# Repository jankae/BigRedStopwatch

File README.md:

# What is it?
* A huge stopwatch with two big red control buttons (start and stop)
* Mainly intended for measuring time on an obstacle course

# How does it work?
* Each button and the display contain a radio module (RFM69)
* Button presses are send to the display which calculates the time

# Further features
* USB charging of the integrated LiPo batteries
* Retransmissions with time compensation if a radio packet gets lost
* Simple highscore management

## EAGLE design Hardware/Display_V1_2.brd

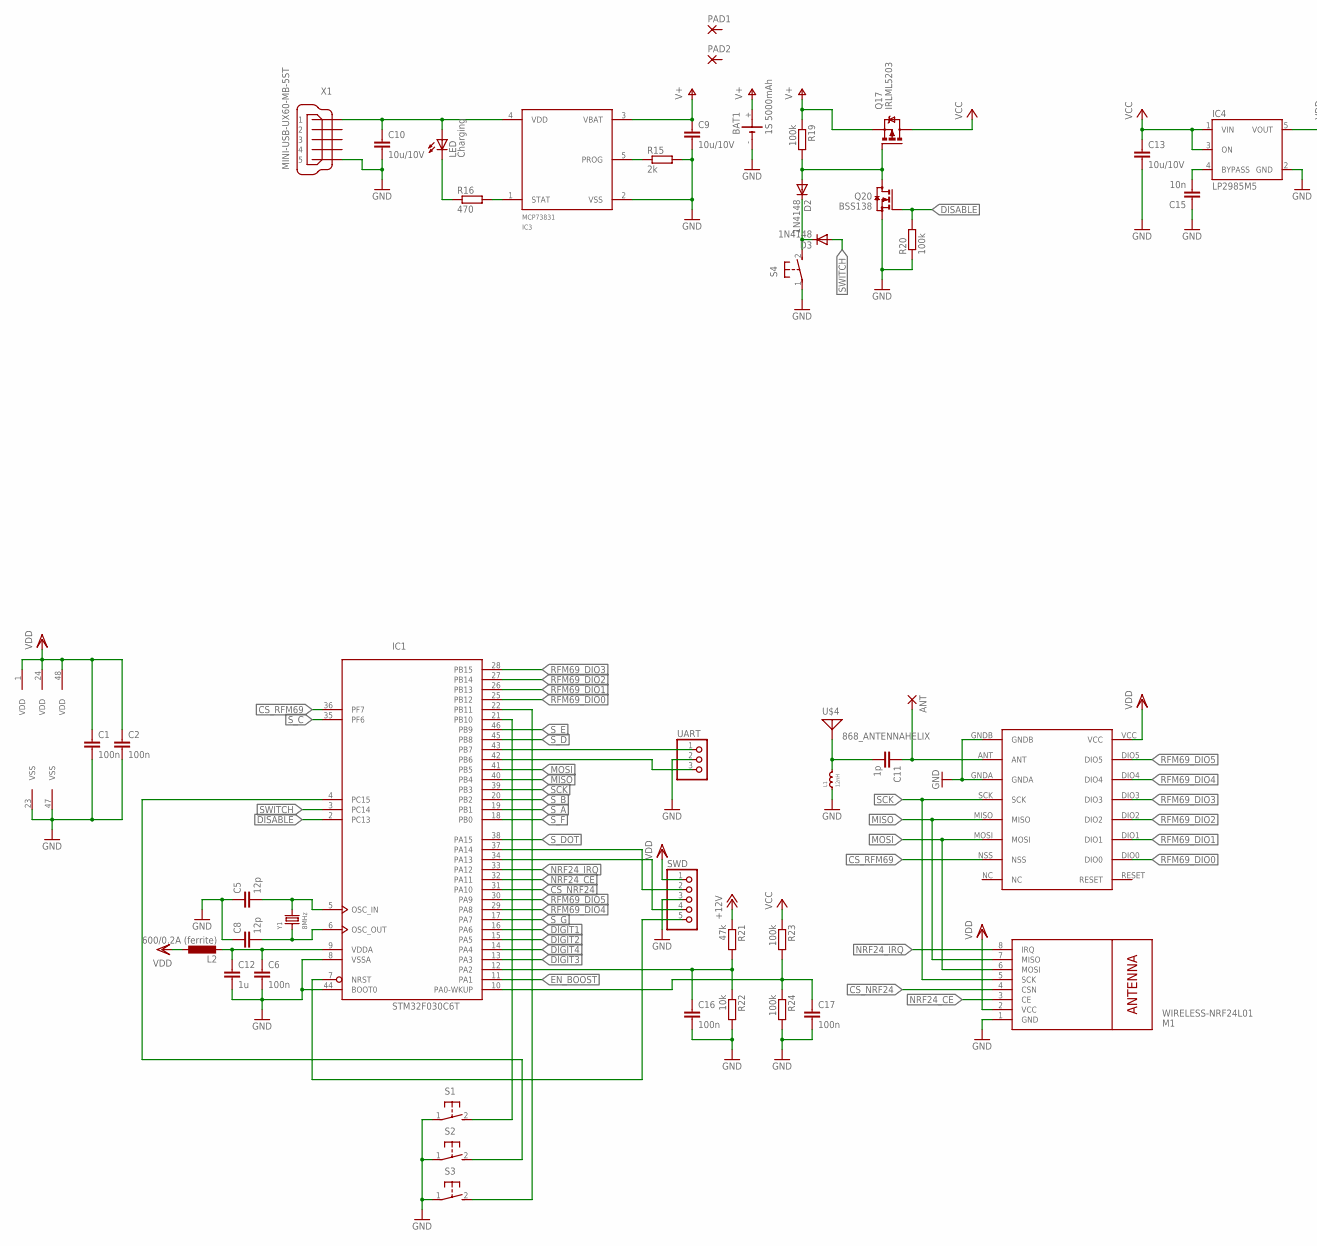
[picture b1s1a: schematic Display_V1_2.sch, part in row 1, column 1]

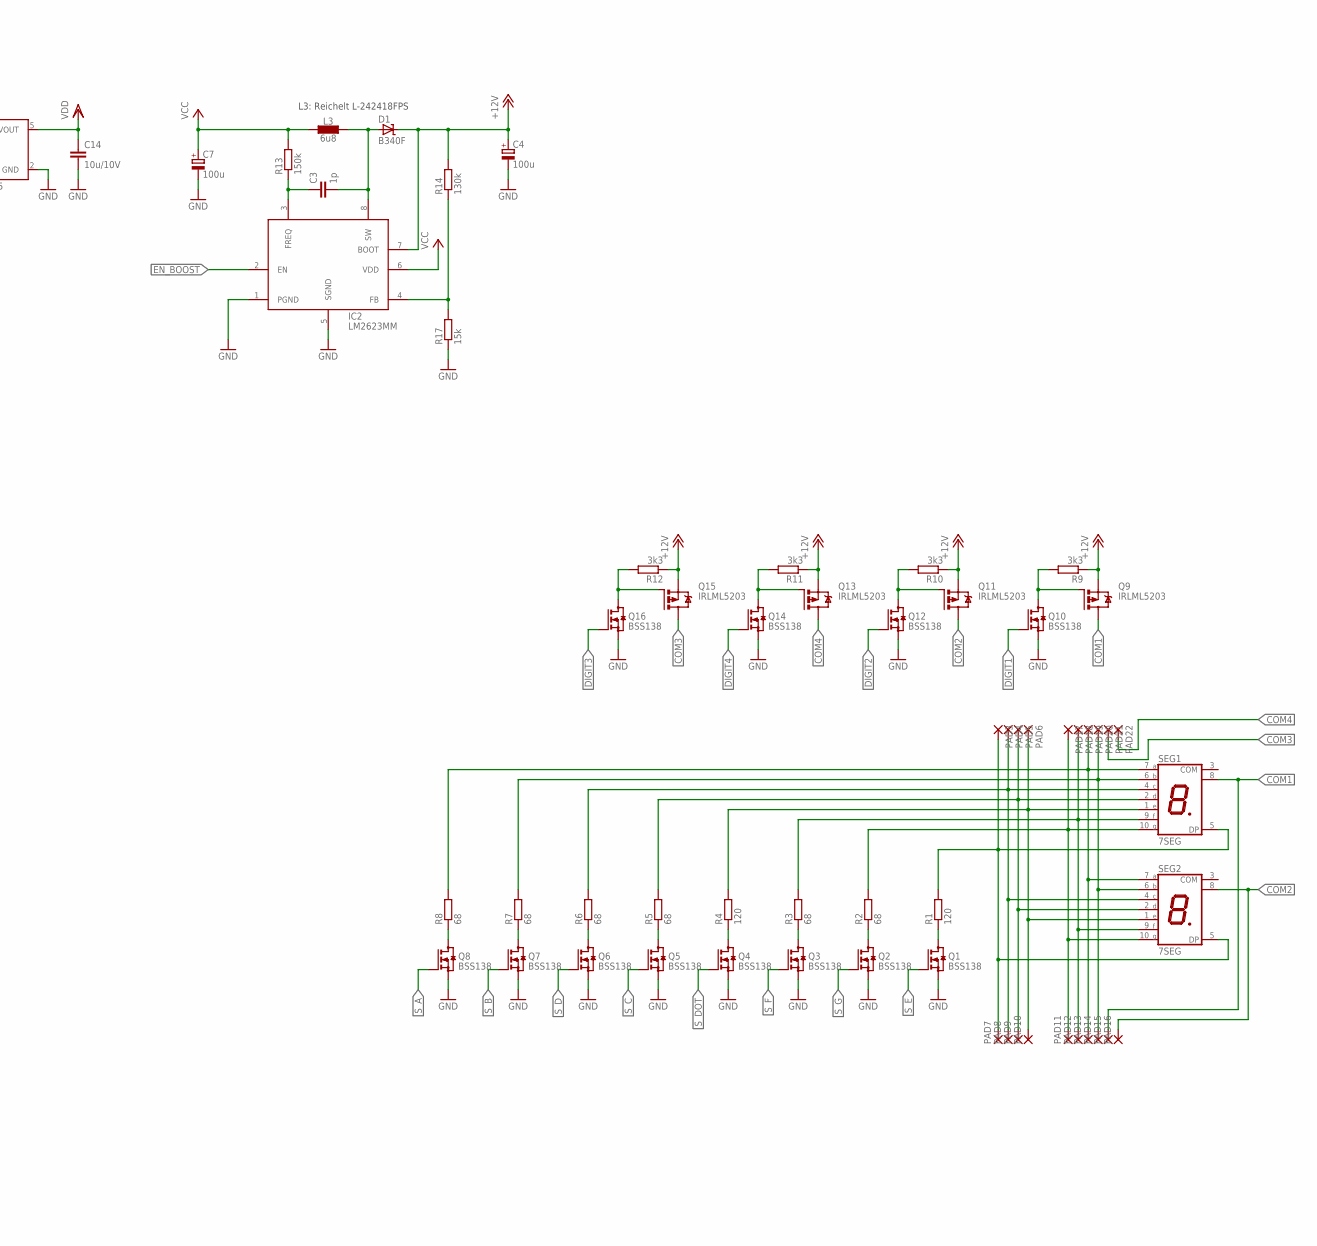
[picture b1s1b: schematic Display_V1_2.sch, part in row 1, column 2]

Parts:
ANT: 1,6/0,8
BAT1: 1S 5000mAh; 1S_5000MAH
C1, C2: 100n; C0603K
C3, C11: 1p; C0603
C4, C7: 100u; 153CLV-0605
C5, C8: 12p; C0603
C6, C16, C17: 100n; C0603
C9, C10, C13, C14: 10u/10V; C1206
C12: 1u; C0603
C15: 10n; C0603
D1: B340F; SMC
D2, D3: 1N4148; MINIMELF
IC1: STM32F030C6T; LQFP48
IC2: LM2623MM; MSOP08
IC3: MCP73831; SOT23-5
IC4: LP2985M5; SOT23-5
L1: 12nH; 0603
L2: 600/0.2A (ferrite); L2012C
L3: 6u8; L_NR60XX
LED: Charging; CHIPLED_0603
M1: WIRELESS-NRF24L01
PAD1, PAD2: 2,54/1,0
PAD3, PAD4, PAD5, PAD6, PAD7, PAD8, PAD9, PAD10, PAD11, PAD12, PAD13, PAD14, PAD15, PAD16, PAD17, PAD18, PAD19, PAD20, PAD21, PAD22: SMD2; SMD1,27-2,54
Q1, Q2, Q3, Q4, Q5, Q6, Q7, Q8, Q10, Q12, Q14, Q16, Q20: BSS138; SOT23
Q9, Q11, Q13, Q15, Q17: IRLML5203; MICRO3
R1, R4: 120; R1206
R2, R3, R5, R6, R7, R8: 68; R1206
R9, R10, R11, R12: 3k3; R0603
R13: 150k; R0603
R14: 130k; R0603
R15: 2k; R0603
R16: 470; R0603
R17: 15k; R0603
R19, R20, R23, R24: 100k; R0603
R21: 47k; R0603
R22: 10k; R0603
S1, S2, S3, S4: 31-XX; B3F-31XX
SEG1, SEG2: 7SEG; 7SEG_70*40
SWD: PINHD-1X5; 1X05
U$1: RFM69HW; RFM
U$4: 868_ANTENNAHELIX; HELIX_868
UART: PINHD-1X3; 1X03
X1: MINI-USB-UX60-MB-5ST; UX60-MB-5ST
Y1: 8MHz; 3.2X2.5MM

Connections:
+12V: C4.+, D1.C, IC2.7 (BOOT), Q9.2 (S), Q11.2 (S), Q13.2 (S), Q15.2 (S), R9.1, R10.1, R11.1, R12.1, R14.2, R21.1
COM1: PAD15.1, Q9.3 (D), SEG1.8 (COM)
COM2: PAD16.1, Q11.3 (D), SEG2.8 (COM)
COM3: PAD21.1, Q15.3 (D)
COM4: PAD22.1, Q13.3 (D)
CS_NRF24: IC1.31 (PA10), M1.4 (CSN)
CS_RFM69: IC1.36 (PF7), U$1.NSS
DIGIT1: IC1.16 (PA6), Q10.1 (G)
DIGIT2: IC1.15 (PA5), Q12.1 (G)
DIGIT3: IC1.13 (PA3), Q16.1 (G)
DIGIT4: IC1.14 (PA4), Q14.1 (G)
DISABLE: IC1.2 (PC13), Q20.1 (G), R20.2
DP: PAD6.1, PAD10.1, R4.2, SEG1.1 (E), SEG2.1 (E)
EN_BOOST: IC1.11 (PA1), IC2.2 (EN)
GND: BAT1.-, C1.2, C2.2, C4.-, C5.1, C6.2, C7.-, C8.1, C9.2, C10.2, C12.2, C13.2, C14.2, C15.1, C16.2, C17.2, IC1.8 (VSSA), IC1.23 (VSS), IC1.44 (BOOT0), IC1.47 (VSS), IC2.1 (PGND), IC2.5 (SGND), IC3.2 (VSS), IC4.2 (GND), L1.1, M1.1 (GND), Q1.2 (S), Q2.2 (S), Q3.2 (S), Q4.2 (S), Q5.2 (S), Q6.2 (S), Q7.2 (S), Q8.2 (S), Q10.2 (S), Q12.2 (S), Q14.2 (S), Q16.2 (S), Q20.2 (S), R15.2, R17.1, R20.1, R22.2, R24.2, S1.1, S2.1, S3.1, S4.1, SWD.3, U$1.GNDA, U$1.GNDB, UART.2, X1.5
MISO: IC1.40 (PB4), M1.7 (MISO), U$1.MISO
MOSI: IC1.41 (PB5), M1.6 (MOSI), U$1.MOSI
unnamed: Q1.3 (D), R1.1
unnamed: Q2.3 (D), R2.1
unnamed: Q3.3 (D), R3.1
unnamed: Q4.3 (D), R4.1
unnamed: Q5.3 (D), R5.1
unnamed: Q6.3 (D), R6.1
unnamed: Q7.3 (D), R7.1
unnamed: Q8.3 (D), R8.1
unnamed: Q9.1 (G), Q10.3 (D), R9.2
unnamed: Q11.1 (G), Q12.3 (D), R10.2
unnamed: Q13.1 (G), Q14.3 (D), R11.2
unnamed: Q15.1 (G), Q16.3 (D), R12.2
unnamed: IC1.21 (PB10), S1.2 (S)
unnamed: C3.1, IC2.3 (FREQ), R13.1
unnamed: C5.2, IC1.5 (OSC_IN), Y1.3 (2)
unnamed: IC1.4 (PC15), S2.2 (S)
unnamed: IC1.22 (PB11), S3.2 (S)
unnamed: C8.2, IC1.6 (OSC_OUT), Y1.1
unnamed: IC3.5 (PROG), R15.1
unnamed: IC3.1 (STAT), R16.2
unnamed: LED.C, R16.1
unnamed: C3.2, D1.A, IC2.8 (SW), L3.2
unnamed: ANT.1, C11.1, U$1.ANT
unnamed: C11.2, L1.2, U$4.ANT, U$4.P$2, U$4.P$3, U$4.P$4, U$4.P$5, U$4.P$6, U$4.P$7, U$4.P$8, U$4.P$9, U$4.P$10, U$4.P$11, U$4.P$12, U$4.P$13, U$4.P$14, U$4.P$15, U$4.P$16, U$4.P$17, U$4.P$18, U$4.P$19, U$4.P$20
unnamed: IC2.4 (FB), R14.1, R17.2
unnamed: D2.A, Q17.1 (G), Q20.3 (D), R19.2
unnamed: C16.1, IC1.12 (PA2), R21.2, R22.1
unnamed: C15.2, IC4.4 (BYPASS)
unnamed: C17.1, IC1.10 (PA0-WKUP), R23.2, R24.1
NRF24_CE: IC1.32 (PA11), M1.3 (CE)
NRF24_IRQ: IC1.33 (PA12), M1.8 (IRQ)
NRST: IC1.7 (NRST), SWD.5
RFM69_DIO0: IC1.25 (PB12), U$1.DIO0
RFM69_DIO1: IC1.26 (PB13), U$1.DIO1
RFM69_DIO2: IC1.27 (PB14), U$1.DIO2
RFM69_DIO3: IC1.28 (PB15), U$1.DIO3
RFM69_DIO4: IC1.29 (PA8), U$1.DIO4
RFM69_DIO5: IC1.30 (PA9), U$1.DIO5
RX: IC1.43 (PB7), UART.1
SCK: IC1.39 (PB3), M1.5 (SCK), U$1.SCK
SEG_A: PAD13.1, PAD19.1, R8.2, SEG1.7 (A), SEG2.7 (A)
SEG_B: PAD14.1, PAD20.1, R7.2, SEG1.6 (B), SEG2.6 (B)
SEG_C: PAD5.1, PAD9.1, R5.2, SEG1.2 (D), SEG2.2 (D)
SEG_D: PAD4.1, PAD8.1, R6.2, SEG1.4 (C), SEG2.4 (C)
SEG_E: PAD3.1, PAD7.1, R1.2, SEG1.5 (DP), SEG2.5 (DP)
SEG_F: PAD12.1, PAD18.1, R3.2, SEG1.9 (F), SEG2.9 (F)
SEG_G: PAD11.1, PAD17.1, R2.2, SEG1.10 (G), SEG2.10 (G)
SWCLK: IC1.37 (PA14), SWD.2
SWDIO: IC1.34 (PA13), SWD.4
SWITCH: D3.A, IC1.3 (PC14)
S_A: IC1.19 (PB1), Q8.1 (G)
S_B: IC1.20 (PB2), Q7.1 (G)
S_C: IC1.35 (PF6), Q5.1 (G)
S_D: IC1.45 (PB8), Q6.1 (G)
S_DOT: IC1.38 (PA15), Q4.1 (G)
S_E: IC1.46 (PB9), Q1.1 (G)
S_F: IC1.18 (PB0), Q3.1 (G)
S_G: IC1.17 (PA7), Q2.1 (G)
TX: IC1.42 (PB6), UART.3
V+: BAT1.+, C9.1, IC3.3 (VBAT), Q17.2 (S), R19.1
VCC: C7.+, C13.1, IC2.6 (VDD), IC4.1 (VIN), IC4.3 (ON), L3.1, Q17.3 (D), R13.2, R23.1
VDD: C1.1, C2.1, C14.1, IC1.1 (VDD), IC1.24 (VDD), IC1.48 (VDD), IC4.5 (VOUT), L2.1, M1.2 (VCC), SWD.1, U$1.VCC
VDDA: C6.1, C12.1, IC1.9 (VDDA), L2.2
VIN: C10.1, IC3.4 (VDD), LED.A, X1.1
_SWITCH: D2.C, D3.C, S4.2 (S)

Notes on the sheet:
L3: Reichelt L-242418FPS

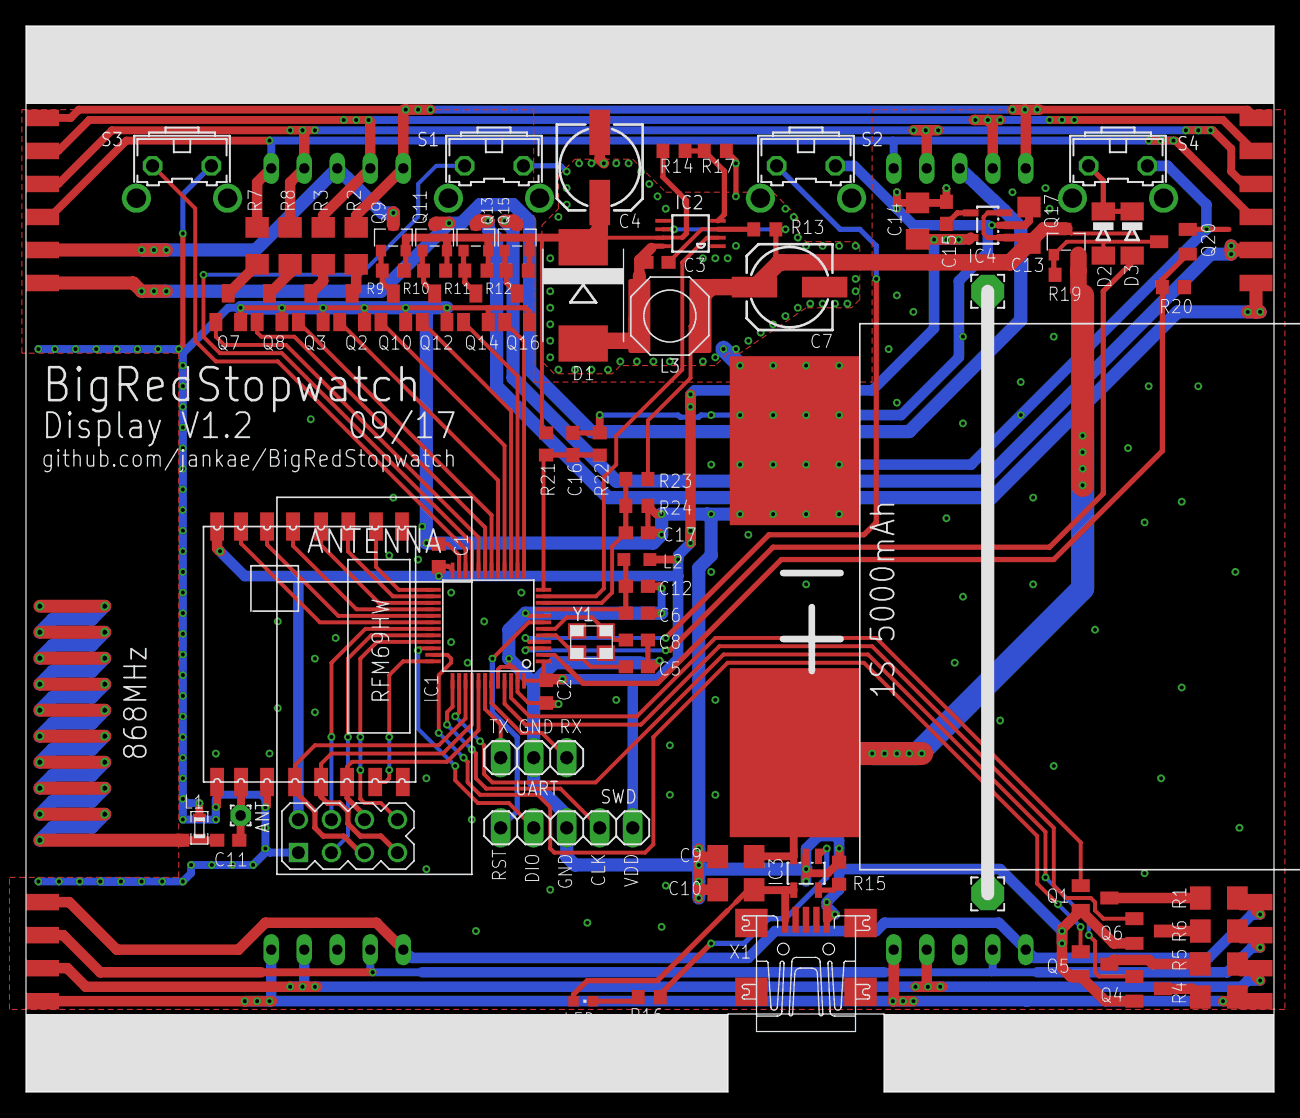
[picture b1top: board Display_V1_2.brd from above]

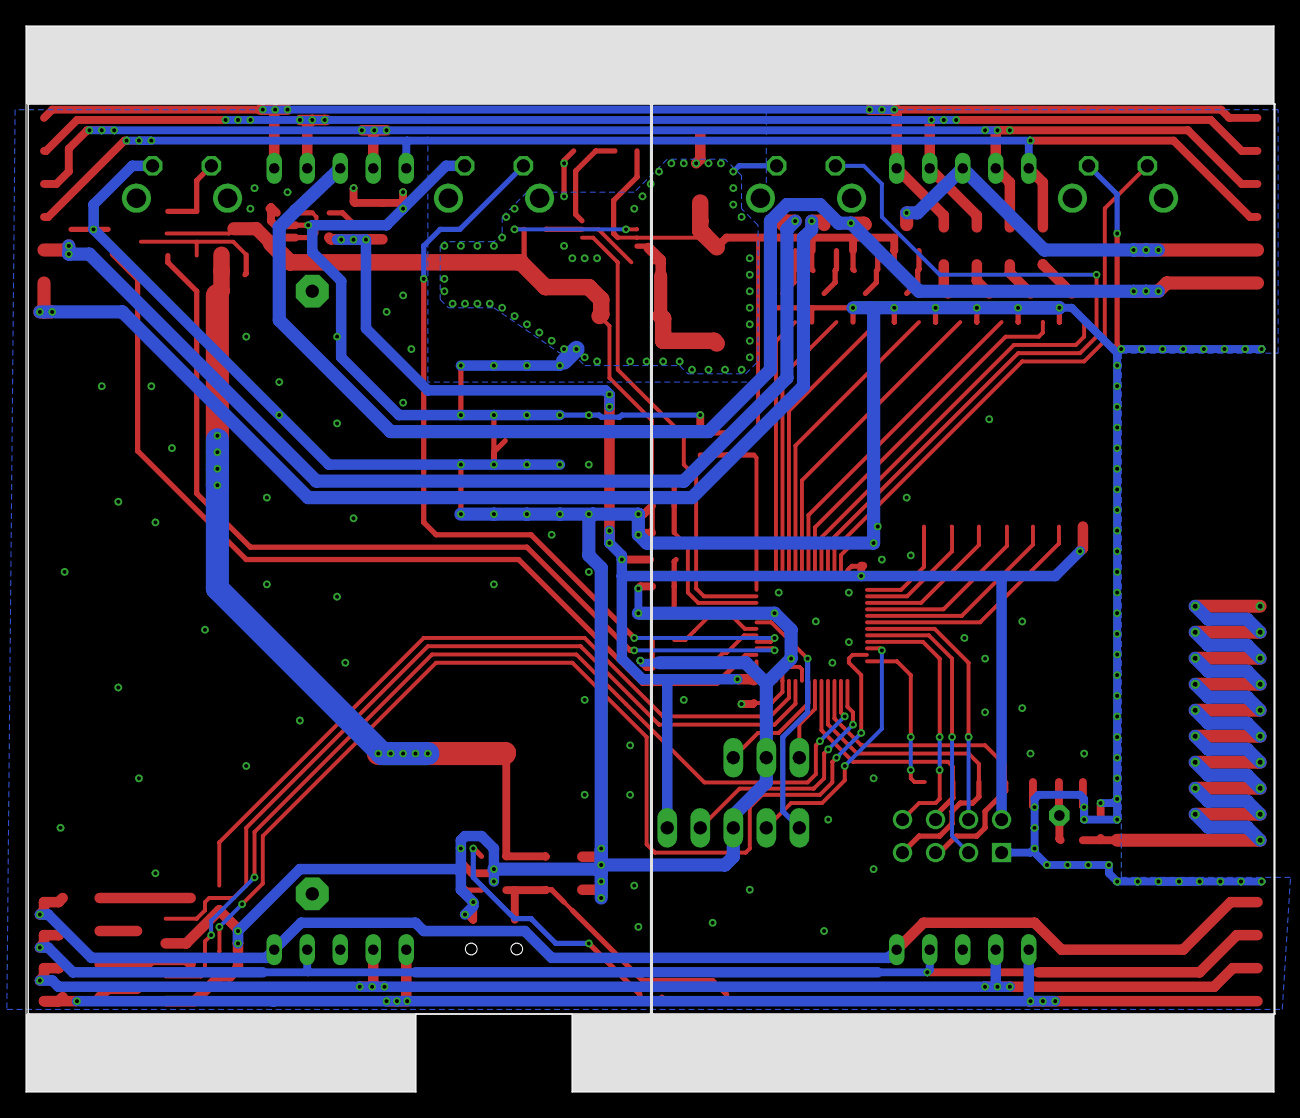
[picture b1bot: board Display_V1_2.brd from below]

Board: 2 copper layers, 96.0 x 82.0 mm, 106 parts (2 on the bottom side), 82 nets.

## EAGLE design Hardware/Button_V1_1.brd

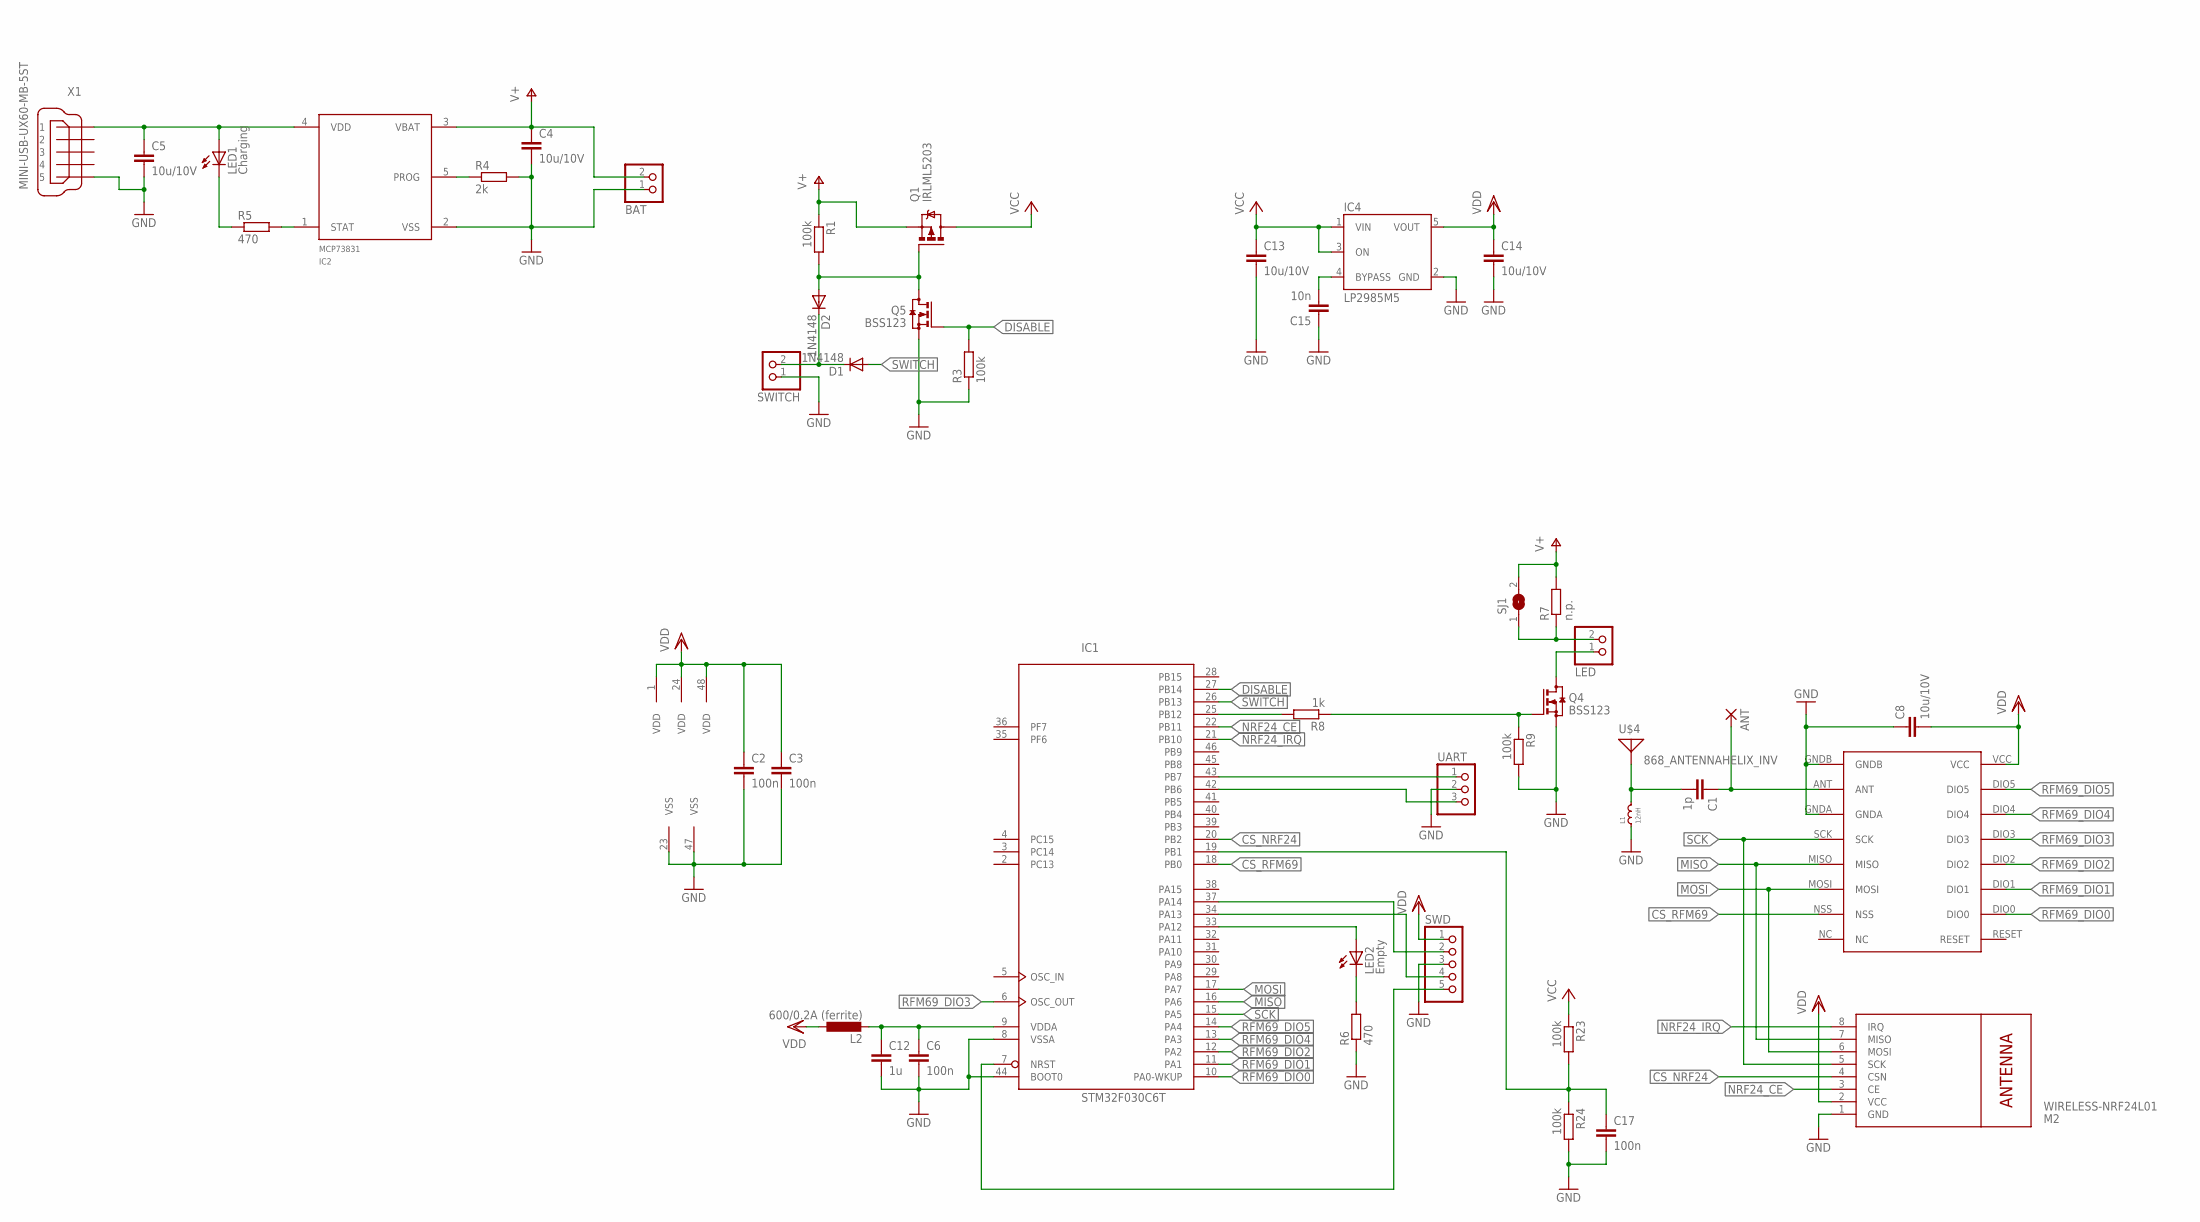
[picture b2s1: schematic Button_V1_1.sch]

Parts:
ANT: 1,6/0,8
BAT: PINHD-1X2; 1X02
C1: 1p; C0603
C2, C3, C6, C17: 100n; C0603
C4, C5, C8, C13, C14: 10u/10V; C1206
C12: 1u; C0603
C15: 10n; C0603
D1, D2: 1N4148; SOD323-W
IC1: STM32F030C6T; LQFP48
IC2: MCP73831; SOT23-5
IC4: LP2985M5; SOT23-5
L1: 12nH; 0603
L2: 600/0.2A (ferrite); L2012C
LED: PINHD-1X2; 1X02
LED1: Charging; CHIPLED_0603
LED2: Empty; CHIPLED_0603
M2: WIRELESS-NRF24L01
Q1: IRLML5203; MICRO3
Q4, Q5: BSS123; SOT23
R1, R3, R9, R23, R24: 100k; R0603
R4: 2k; R0603
R5, R6: 470; R0603
R7: n.p.; R1206
R8: 1k; R0603
SJ1: SJ
SWD: PINHD-1X5; 1X05
SWITCH: PINHD-1X2; 1X02
U$1: RFM69HW; RFM
U$4: 868_ANTENNAHELIX_INV; HELIX_868_INV
UART: PINHD-1X3; 1X03
X1: MINI-USB-UX60-MB-5ST; UX60-MB-5ST

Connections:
CS_NRF24: IC1.20 (PB2), M2.4 (CSN)
CS_RFM69: IC1.18 (PB0), U$1.NSS
DISABLE: IC1.27 (PB14), Q5.1 (G), R3.2
GND: BAT.1, C2.2, C3.2, C4.2, C5.2, C6.2, C8.1, C12.2, C13.2, C14.2, C15.1, C17.2, IC1.8 (VSSA), IC1.23 (VSS), IC1.44 (BOOT0), IC1.47 (VSS), IC2.2 (VSS), IC4.2 (GND), L1.1, M2.1 (GND), Q4.2 (S), Q5.2 (S), R3.1, R4.2, R6.1, R9.2, R24.2, SWD.3, SWITCH.1, U$1.GNDA, U$1.GNDB, UART.2, X1.5
MISO: IC1.16 (PA6), M2.7 (MISO), U$1.MISO
MOSI: IC1.17 (PA7), M2.6 (MOSI), U$1.MOSI
unnamed: D2.A, Q1.1 (G), Q5.3 (D), R1.2
unnamed: IC2.5 (PROG), R4.1
unnamed: ANT.1, C1.1, U$1.ANT
unnamed: C1.2, L1.2, U$4.ANT, U$4.P$2, U$4.P$3, U$4.P$4, U$4.P$5, U$4.P$6, U$4.P$7, U$4.P$8, U$4.P$9, U$4.P$10, U$4.P$11, U$4.P$12, U$4.P$13, U$4.P$14, U$4.P$15, U$4.P$16, U$4.P$17, U$4.P$18, U$4.P$19, U$4.P$20
unnamed: LED2.C, R6.2
unnamed: IC2.1 (STAT), R5.2
unnamed: IC1.33 (PA12), LED2.A
unnamed: LED1.C, R5.1
unnamed: LED.1, Q4.3 (D)
unnamed: LED.2, R7.1, SJ1.1
unnamed: Q4.1 (G), R8.1, R9.1
unnamed: IC1.25 (PB12), R8.2
unnamed: C15.2, IC4.4 (BYPASS)
unnamed: C17.1, IC1.19 (PB1), R23.2, R24.1
NRF24_CE: IC1.22 (PB11), M2.3 (CE)
NRF24_IRQ: IC1.21 (PB10), M2.8 (IRQ)
NRST: IC1.7 (NRST), SWD.5
RFM69_DIO0: IC1.10 (PA0-WKUP), U$1.DIO0
RFM69_DIO1: IC1.11 (PA1), U$1.DIO1
RFM69_DIO2: IC1.12 (PA2), U$1.DIO2
RFM69_DIO3: IC1.6 (OSC_OUT), U$1.DIO3
RFM69_DIO4: IC1.13 (PA3), U$1.DIO4
RFM69_DIO5: IC1.14 (PA4), U$1.DIO5
RX: IC1.43 (PB7), UART.1
SCK: IC1.15 (PA5), M2.5 (SCK), U$1.SCK
SWCLK: IC1.37 (PA14), SWD.2
SWDIO: IC1.34 (PA13), SWD.4
SWITCH: D1.A, IC1.26 (PB13)
TX: IC1.42 (PB6), UART.3
V+: BAT.2, C4.1, IC2.3 (VBAT), Q1.2 (S), R1.1, R7.2, SJ1.2
VCC: C13.1, IC4.1 (VIN), IC4.3 (ON), Q1.3 (D), R23.1
VDD: C2.1, C3.1, C8.2, C14.1, IC1.1 (VDD), IC1.24 (VDD), IC1.48 (VDD), IC4.5 (VOUT), L2.1, M2.2 (VCC), SWD.1, U$1.VCC
VDDA: C6.1, C12.1, IC1.9 (VDDA), L2.2
VIN: C5.1, IC2.4 (VDD), LED1.A, X1.1
_SWITCH: D1.C, D2.C, SWITCH.2

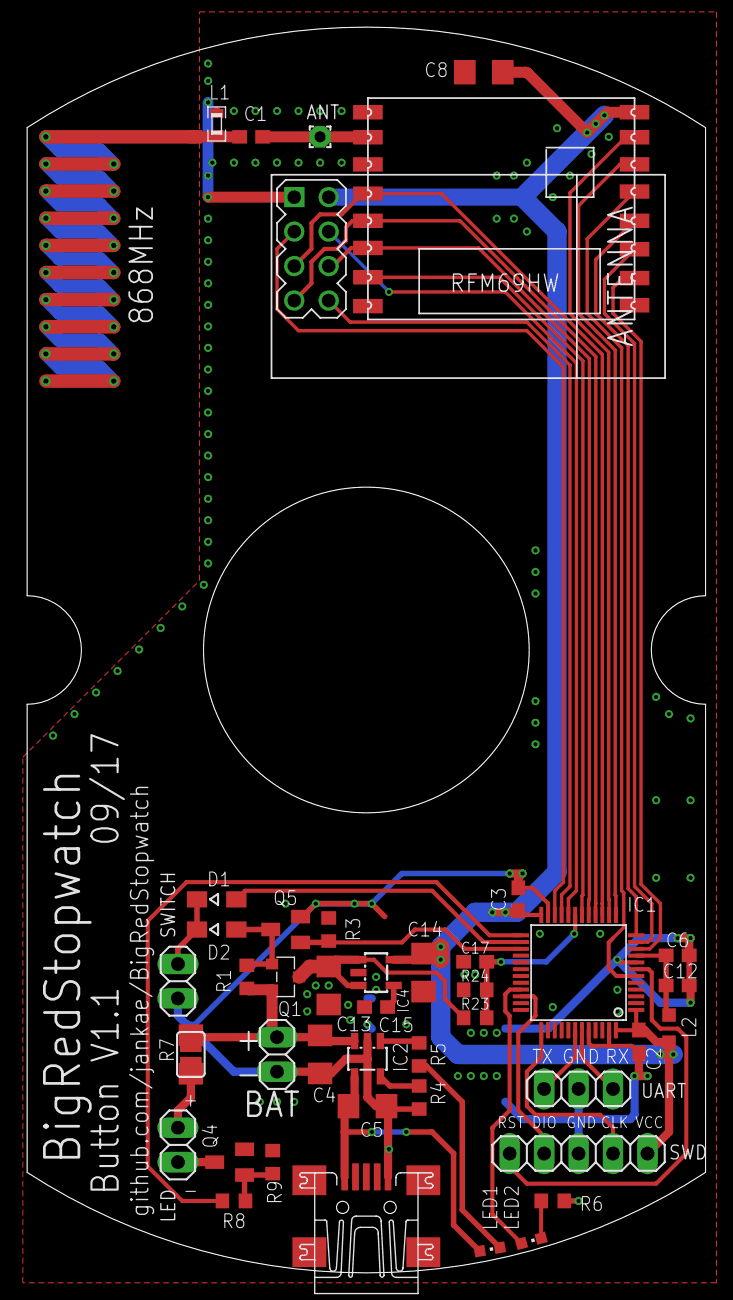
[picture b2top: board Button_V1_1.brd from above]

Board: 2 copper layers, 50.0 x 91.8 mm, 45 parts (0 on the bottom side), 41 nets.

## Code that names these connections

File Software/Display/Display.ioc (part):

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Mcu.Name=STM32F030C8Tx
Mcu.Package=LQFP48
Mcu.UserName=STM32F030C8Tx
PA0.GPIOParameters=GPIO_Label
PA0.GPIO_Label=BATTERY_SENSE
PA0.Mode=IN0
PA0.Signal=ADC_IN0
PA1.GPIOParameters=GPIO_Label
PA1.GPIO_Label=BOOST_ENABLE
PA1.Signal=GPIO_Output
PA10.GPIOParameters=GPIO_Speed,GPIO_Label
PA10.GPIO_Label=CS_NRF24
PA10.GPIO_Speed=GPIO_SPEED_FREQ_HIGH
PA10.Signal=GPIO_Output
PA11.GPIOParameters=GPIO_Label
PA11.GPIO_Label=NRF24_CE
PA11.Signal=GPIO_Output
PA12.GPIOParameters=GPIO_PuPd,GPIO_Label
PA12.GPIO_Label=NRF24_IRQ
PA12.GPIO_PuPd=GPIO_PULLDOWN
PA12.Signal=GPIO_Input
PA15.GPIOParameters=GPIO_Speed,GPIO_Label
PA15.GPIO_Label=SEGMENT_DOT
PA15.GPIO_Speed=GPIO_SPEED_FREQ_HIGH
PA15.Signal=GPIO_Output
PA2.GPIOParameters=GPIO_Label
PA2.GPIO_Label=BOOST_SENSE
PA2.Mode=IN2
PA2.Signal=ADC_IN2
PA3.GPIOParameters=GPIO_Speed,GPIO_Label
PA3.GPIO_Label=DIGIT3
PA3.GPIO_Speed=GPIO_SPEED_FREQ_HIGH
PA3.Signal=GPIO_Output
PA4.GPIOParameters=GPIO_Speed,GPIO_Label
PA4.GPIO_Label=DIGIT4
PA4.GPIO_Speed=GPIO_SPEED_FREQ_HIGH
PA4.Signal=GPIO_Output
PA5.GPIOParameters=GPIO_Speed,GPIO_Label
PA5.GPIO_Label=DIGIT2
PA5.GPIO_Speed=GPIO_SPEED_FREQ_HIGH
PA5.Signal=GPIO_Output
PA6.GPIOParameters=GPIO_Speed,GPIO_Label
PA6.GPIO_Label=DIGIT1
PA6.GPIO_Speed=GPIO_SPEED_FREQ_HIGH
PA6.Signal=GPIO_Output
PA7.GPIOParameters=GPIO_Speed,GPIO_Label
PA7.GPIO_Label=SEGMENT_G
PA7.GPIO_Speed=GPIO_SPEED_FREQ_HIGH
PA7.Signal=GPIO_Output
PA8.GPIOParameters=GPIO_PuPd,GPIO_Label
PA8.GPIO_Label=RFM69_DIO4
PA8.GPIO_PuPd=GPIO_PULLDOWN
PA8.Signal=GPIO_Input
PA9.GPIOParameters=GPIO_PuPd,GPIO_Label
PA9.GPIO_Label=RFM69_DIO5
PA9.GPIO_PuPd=GPIO_PULLDOWN
PA9.Signal=GPIO_Input
PB0.GPIOParameters=GPIO_Speed,GPIO_Label
PB0.GPIO_Label=SEGMENT_F
PB0.GPIO_Speed=GPIO_SPEED_FREQ_HIGH
PB0.Signal=GPIO_Output
PB1.GPIOParameters=GPIO_Speed,GPIO_Label
PB1.GPIO_Label=SEGMENT_A
PB1.GPIO_Speed=GPIO_SPEED_FREQ_HIGH
PB1.Signal=GPIO_Output
PB10.GPIOParameters=GPIO_PuPd,GPIO_Label
PB10.GPIO_Label=SWITCH1
PB10.GPIO_PuPd=GPIO_PULLUP
PB10.Signal=GPIO_Input
PB11.GPIOParameters=GPIO_PuPd,GPIO_Label
PB11.GPIO_Label=SWITCH3
PB11.GPIO_PuPd=GPIO_PULLUP
PB11.Signal=GPIO_Input
PB12.GPIOParameters=GPIO_PuPd,GPIO_Label
PB12.GPIO_Label=RFM69_DIO0
PB12.GPIO_PuPd=GPIO_PULLDOWN
PB12.Signal=GPXTI12
PB13.GPIOParameters=GPIO_PuPd,GPIO_Label
PB13.GPIO_Label=RFM69_DIO1
PB13.GPIO_PuPd=GPIO_PULLDOWN
PB13.Signal=GPIO_Input
PB14.GPIOParameters=GPIO_PuPd,GPIO_Label
PB14.GPIO_Label=RFM69_DIO2
PB14.GPIO_PuPd=GPIO_PULLDOWN
PB14.Signal=GPIO_Input
PB15.GPIOParameters=GPIO_PuPd,GPIO_Label
PB15.GPIO_Label=RFM69_DIO3
PB15.GPIO_PuPd=GPIO_PULLDOWN
PB15.Signal=GPIO_Input
PB2.GPIOParameters=GPIO_Speed,GPIO_Label
PB2.GPIO_Label=SEGMENT_B
PB2.GPIO_Speed=GPIO_SPEED_FREQ_HIGH
PB2.Signal=GPIO_Output
PB3.Mode=Full_Duplex_Master
PB3.Signal=SPI1_SCK
PB4.Mode=Full_Duplex_Master
PB4.Signal=SPI1_MISO
PB5.Mode=Full_Duplex_Master
PB5.Signal=SPI1_MOSI
PB6.Mode=Asynchronous
PB6.Signal=USART1_TX
PB7.Mode=Asynchronous
PB7.Signal=USART1_RX
PB8.GPIOParameters=GPIO_Speed,GPIO_Label
PB8.GPIO_Label=SEGMENT_D
PB8.GPIO_Speed=GPIO_SPEED_FREQ_HIGH
PB8.Signal=GPIO_Output
PB9.GPIOParameters=GPIO_Speed,GPIO_Label
PB9.GPIO_Label=SEGMENT_E
PB9.GPIO_Speed=GPIO_SPEED_FREQ_HIGH
PB9.Signal=GPIO_Output
PC13.GPIOParameters=PinState,GPIO_Label
PC13.GPIO_Label=DISABLE
PC13.PinState=GPIO_PIN_SET
PC13.Signal=GPIO_Output
PC14-OSC32_IN.GPIOParameters=GPIO_PuPd,GPIO_Label
PC14-OSC32_IN.GPIO_Label=SWITCH_ONOFF
PC14-OSC32_IN.GPIO_PuPd=GPIO_PULLUP
PC14-OSC32_IN.Signal=GPIO_Input
PC15-OSC32_OUT.GPIOParameters=GPIO_PuPd,GPIO_Label
PC15-OSC32_OUT.GPIO_Label=SWITCH2
PC15-OSC32_OUT.GPIO_PuPd=GPIO_PULLUP
PC15-OSC32_OUT.Signal=GPIO_Input
PF0-OSC_IN.Mode=HSE-External-Oscillator
PF0-OSC_IN.Signal=RCC_OSC_IN
PF1-OSC_OUT.Mode=HSE-External-Oscillator
PF1-OSC_OUT.Signal=RCC_OSC_OUT
PF6.GPIOParameters=GPIO_Speed,GPIO_Label
PF6.GPIO_Label=SEGMENT_C
PF6.GPIO_Speed=GPIO_SPEED_FREQ_HIGH
PF6.Signal=GPIO_Output
PF7.GPIOParameters=GPIO_Speed,GPIO_Label
PF7.GPIO_Label=CS_RFM69
PF7.GPIO_Speed=GPIO_SPEED_FREQ_HIGH
PF7.Signal=GPIO_Output
RCC.HSE_VALUE=16000000
RCC.SYSCLKFreq_VALUE=16000000
RCC.SYSCLKSource=RCC_SYSCLKSOURCE_HSE
board=Display

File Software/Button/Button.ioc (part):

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Mcu.Name=STM32F030C8Tx
Mcu.Package=LQFP48
Mcu.UserName=STM32F030C8Tx
PA0.GPIOParameters=GPIO_PuPd,GPIO_Label
PA0.GPIO_Label=DIO0
PA0.GPIO_PuPd=GPIO_PULLDOWN
PA0.Signal=GPXTI0
PA1.GPIOParameters=GPIO_PuPd,GPIO_Label
PA1.GPIO_Label=DIO1
PA1.GPIO_PuPd=GPIO_PULLDOWN
PA1.Signal=GPIO_Input
PA12.GPIOParameters=GPIO_Label
PA12.GPIO_Label=ERROR_LED
PA12.Signal=GPIO_Output
PA13.Mode=Serial_Wire
PA13.Signal=SYS_SWDIO
PA14.Mode=Serial_Wire
PA14.Signal=SYS_SWCLK
PA2.GPIOParameters=GPIO_PuPd,GPIO_Label
PA2.GPIO_Label=DIO2
PA2.GPIO_PuPd=GPIO_PULLDOWN
PA2.Signal=GPIO_Input
PA3.GPIOParameters=GPIO_PuPd,GPIO_Label
PA3.GPIO_Label=DIO4
PA3.GPIO_PuPd=GPIO_PULLDOWN
PA3.Signal=GPIO_Input
PA4.GPIOParameters=GPIO_PuPd,GPIO_Label
PA4.GPIO_Label=DIO5
PA4.GPIO_PuPd=GPIO_PULLDOWN
PA4.Signal=GPIO_Input
PA5.Mode=Full_Duplex_Master
PA5.Signal=SPI1_SCK
PA6.Mode=Full_Duplex_Master
PA6.Signal=SPI1_MISO
PA7.Mode=Full_Duplex_Master
PA7.Signal=SPI1_MOSI
PB0.GPIOParameters=GPIO_Speed,GPIO_Label
PB0.GPIO_Label=CS_RFM
PB0.GPIO_Speed=GPIO_SPEED_FREQ_HIGH
PB0.Signal=GPIO_Output
PB1.GPIOParameters=GPIO_Label
PB1.GPIO_Label=BATTERY_SENSE
PB1.Mode=IN9
PB1.Signal=ADC_IN9
PB12.GPIOParameters=GPIO_Label
PB12.GPIO_Label=BUTTON_LED
PB12.Signal=GPIO_Output
PB13.GPIOParameters=GPIO_PuPd,GPIO_Label
PB13.GPIO_Label=SWITCH
PB13.GPIO_PuPd=GPIO_PULLUP
PB13.Signal=GPIO_Input
PB14.GPIOParameters=PinState,GPIO_Label
PB14.GPIO_Label=DISABLE
PB14.PinState=GPIO_PIN_SET
PB14.Signal=GPIO_Output
PB6.Mode=Asynchronous
PB6.Signal=USART1_TX
PB7.Mode=Asynchronous
PB7.Signal=USART1_RX
PF1-OSC_OUT.GPIOParameters=GPIO_PuPd,GPIO_Label
PF1-OSC_OUT.GPIO_Label=DIO3
PF1-OSC_OUT.GPIO_PuPd=GPIO_PULLDOWN
PF1-OSC_OUT.Signal=GPIO_Input
board=Button

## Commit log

2017-07-21 Display template + initial Hard+Software
2017-07-22 Radio template + beginning of stopwatch
2017-07-25 Further software (Switches, HAL)
2017-07-29 Added crystal to display board
2017-07-29 Button Layout done
2017-07-29 Initial CubeMX button
2017-07-29 LED output added to button
2017-07-30 Second iteration of display board
2017-08-01 3V LDO + voltage sensing
2017-08-01 last(?) changes
2017-08-10 Final PCB changes
2017-08-11 CubeMX adjusted to layout changes
2017-08-11 Changes to gitignore and makefiles
2017-09-03 Slight changes for easier fabrication
2017-09-03 Untested firmware of button
2017-09-03 pass switch number instead of switch
2017-09-03 Use random numbers for ID
2017-09-10 Cosmetic changes
2017-09-11 C to C++ in Display project
2017-09-11 Store permanent data in Flash + minor optimizations
2017-09-12 Main display application
2017-09-12 Battery and system fault handling
2017-09-16 Bugfixes and improvements, basic system working
2017-09-17 Auto-turnoff + display battery voltage at startup
2017-09-17 New board revisions (Supply fixes)
2017-09-19 First pictures of the display
2017-11-13 Abort running clock by pressing start multiple times
2019-07-10 Eagle version update
2019-11-18 more pictures

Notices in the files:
parts and their libraries:
diy-modules: Released under the Creative Commons Attribution 4.0 International License: http://creativecommons.org/licenses/by/4.0
